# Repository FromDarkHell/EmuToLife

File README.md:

## EmuToLife

EmuToLife is a USB emulator for LEGO Dimensions, Disney Infinity, *and* [Kamen Rider Summonride](https://kamenrider.fandom.com/wiki/Kamen_Rider_Summonride).

It lets you use a Raspberry Pi Pico 2W (or W) as a replacement for an official toys-to-life pad. 
With this, you can play the game on PS3/Wii U/PS4, *or* (retail!) Xbox 360, without the original playpad.

### Setup

1. Purchase a Pi Pico 2W, and plug it in while holding the BOOTSEL button
2. Drag/drop the `.uf2` (available on Github Releases) onto the new USB device
    - If successful, the Pico will restart.
3. On the first boot, the Pico will create a new WiFi network named `captive`.
    - Connect to the `captive` WiFi network, and it will bring you to a captive portal

4. From here, it will restart, and conect to your home WiFi.
5. Then, afterwards, you can connect to it via mDNS by going to `emupad.local` in a browser.

### Features

- Wi-Fi captive portal for first-time setup
- Local web UI for managing the toy/character portal (spawning tags, etc.)
- Tag reading/writing/etc handled by my [ToysToLifeLib](https://github.com/FromDarkHell/ToysToLifeLib) library
- Full **retail** Xbox 360 support, powered by [libxsm3](https://github.com/InvoxiPlayGames/libxsm3/) by [InvoxiPlayGames](https://github.com/InvoxiPlayGames)

### License

This project is licensed using [MIT](/LICENSE.md)
- This project directly includes [libxsm3](https://github.com/InvoxiPlayGames/libxsm3/), which is licensed under GNU Lesser General Public License version 2.1
    * Additionally, libxsm3 uses [ExCrypt](https://github.com/emoose/ExCrypt), licensed under the 3-clause BSD license
- A large chunk of the LEGO Dimensions implementation is based on [Berny23/LD-ToyPad-Emulator](https://github.com/Berny23/LD-ToyPad-Emulator/), alongside [node-ld](https://github.com/Berny23/node-ld)

### Support

If you for some reason want to support me financially for this project (or others I make), you can donate to me via [ko-fi](https://ko-fi.com/fromdarkhell) or [Patreon](https://patreon.com/fromdarkhell).

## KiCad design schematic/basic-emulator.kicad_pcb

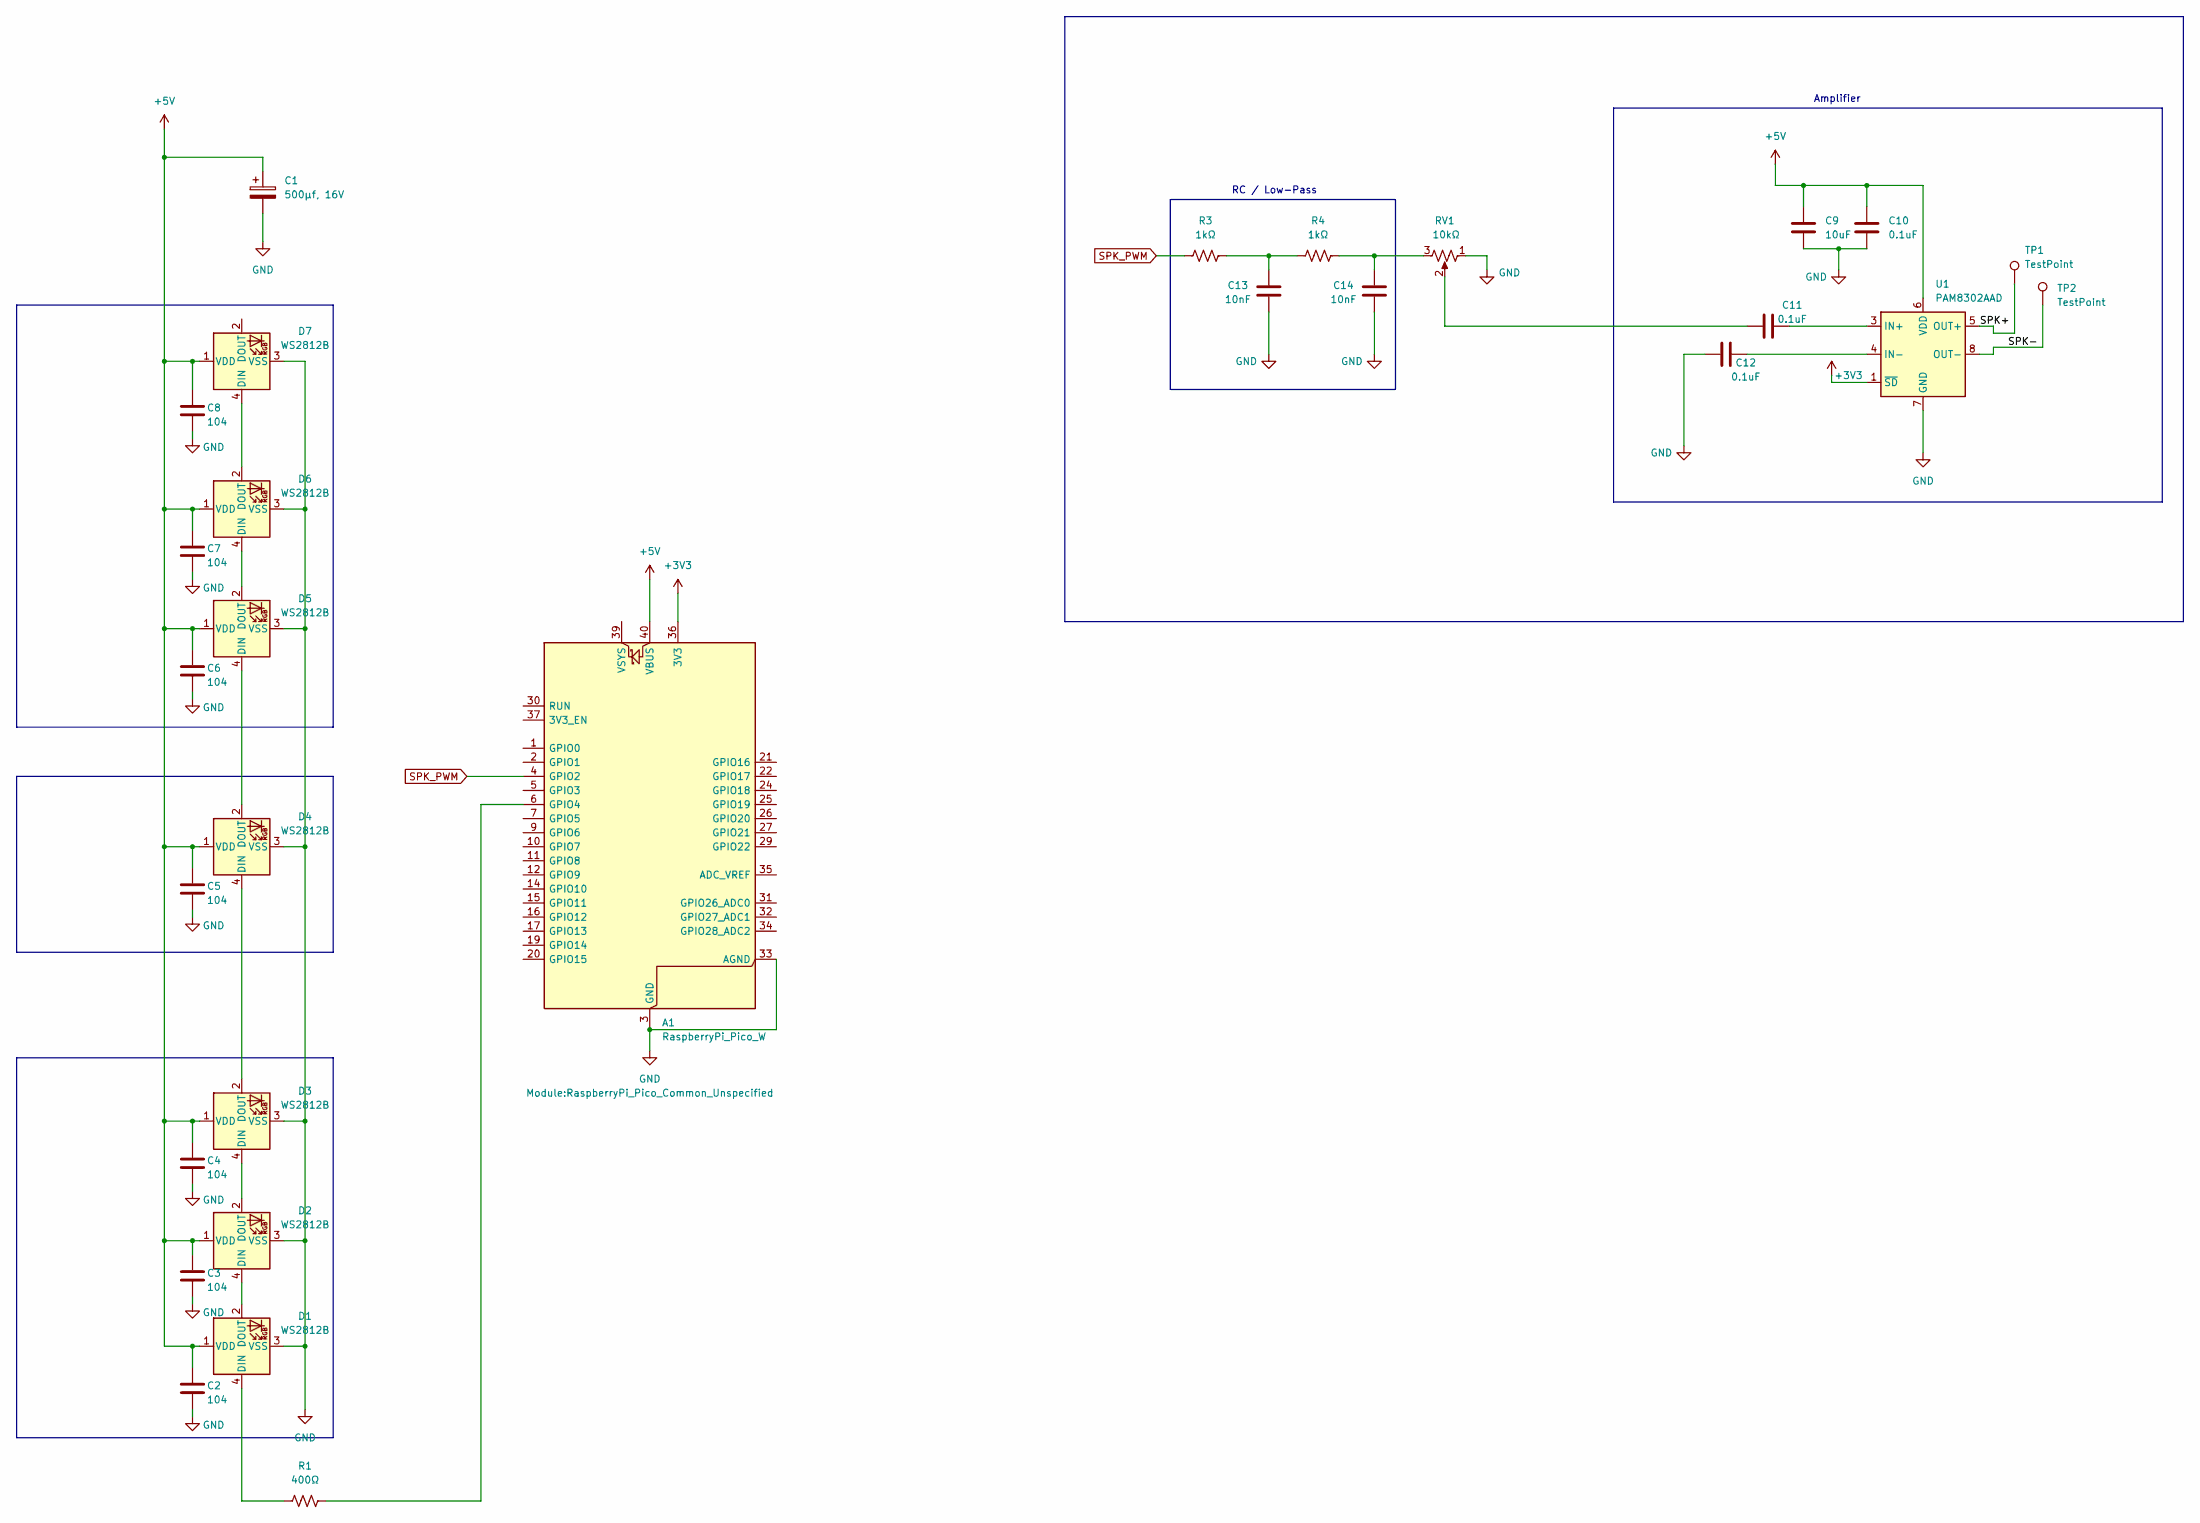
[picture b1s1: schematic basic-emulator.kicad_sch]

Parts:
A1: RaspberryPi_Pico_W; RaspberryPi_Pico_Common_Unspecified
C1: 500µf, 16V; CP_Radial_D8.0mm_P5.00mm
C2, C3, C4, C5, C6, C7, C8: 104; C_1206_3216Metric_Pad1.33x1.80mm_HandSolder
C9: 10uF; C_0603_1608Metric_Pad1.08x0.95mm_HandSolder
C10, C11, C12: 0.1uF; C_0603_1608Metric_Pad1.08x0.95mm_HandSolder
C13, C14: 10nF; C_0603_1608Metric_Pad1.08x0.95mm_HandSolder
D1, D2, D3, D4, D5, D6, D7: WS2812B; LED_WS2812B_PLCC4_5.0x5.0mm_P3.2mm
R1: 400Ω; R_1206_3216Metric_Pad1.30x1.75mm_HandSolder
R3, R4: 1kΩ; R_0603_1608Metric_Pad0.98x0.95mm_HandSolder
RV1: 10kΩ; Potentiometer_Bourns_3314G_Vertical
TP1, TP2: TestPoint; TestPoint_Pad_D2.0mm
U1: PAM8302AAD; SOIC-8_3.9x4.9mm_P1.27mm

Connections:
+3V3: A1.36 (3V3), U1.1 (~SD)
+5V: A1.40 (VBUS), C1.1, C2.1, C3.1, C4.1, C5.1, C6.1, C7.1, C8.1, C9.1, C10.1, D1.1 (VDD), D2.1 (VDD), D3.1 (VDD), D4.1 (VDD), D5.1 (VDD), D6.1 (VDD), D7.1 (VDD), U1.6 (VDD)
/SPK+: TP1.1 (1_1), U1.5 (OUT+)
/SPK-: TP2.1 (1_1), U1.8 (OUT-)
GND: A1.3 (GND), A1.8 (GND), A1.13 (GND), A1.18 (GND), A1.23 (GND), A1.28 (GND), A1.33 (AGND), A1.38 (GND), C1.2, C2.2, C3.2, C4.2, C5.2, C6.2, C7.2, C8.2, C9.2, C10.2, C12.1, C13.2, C14.2, D1.3 (VSS), D2.3 (VSS), D3.3 (VSS), D4.3 (VSS), D5.3 (VSS), D6.3 (VSS), D7.3 (VSS), RV1.1, U1.7 (GND)
unnamed: A1.6 (GPIO4), R1.2
unnamed: C11.1, RV1.2
unnamed: C13.1, R3.2, R4.1
unnamed: C14.1, R4.2, RV1.3
unnamed: D1.4 (DIN), R1.1
unnamed: D1.2 (DOUT), D2.4 (DIN)
unnamed: D2.2 (DOUT), D3.4 (DIN)
unnamed: D3.2 (DOUT), D4.4 (DIN)
unnamed: D4.2 (DOUT), D5.4 (DIN)
unnamed: D5.2 (DOUT), D6.4 (DIN)
unnamed: D6.2 (DOUT), D7.4 (DIN)
unnamed: C11.2, U1.3 (IN+)
unnamed: C12.2, U1.4 (IN-)
SPK_PWM: A1.4 (GPIO2), R3.1

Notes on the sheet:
RC / Low-Pass
Amplifier

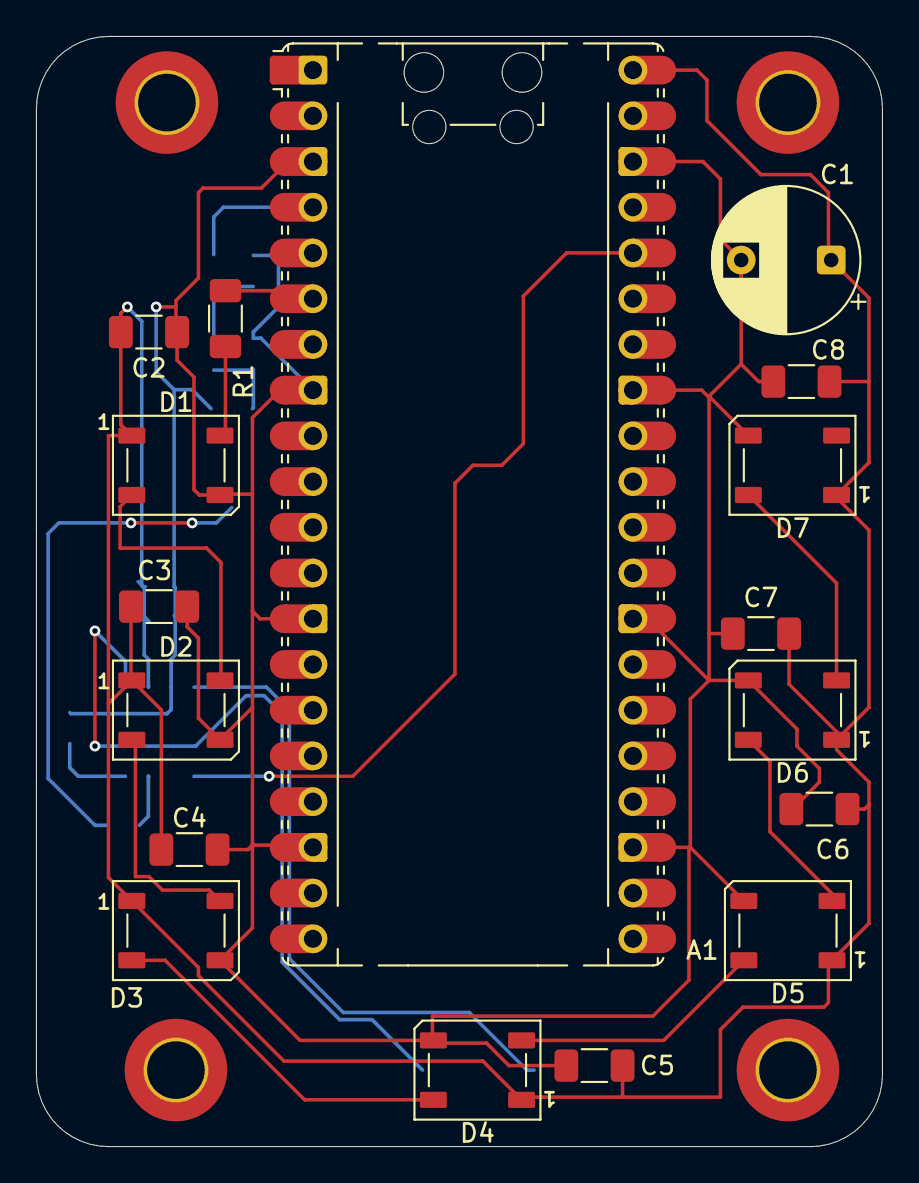
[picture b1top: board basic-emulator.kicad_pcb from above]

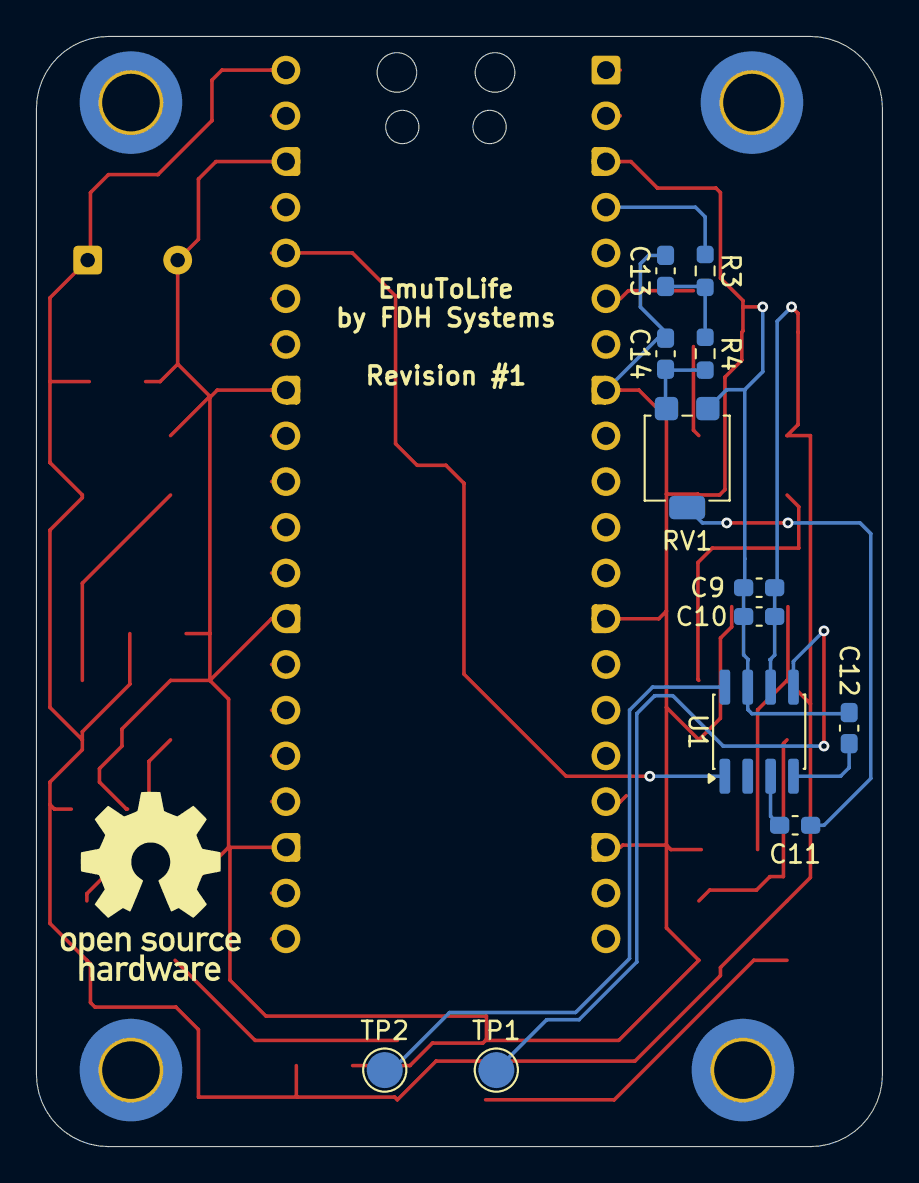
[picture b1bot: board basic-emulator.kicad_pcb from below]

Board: 2 copper layers, 47.0 x 61.7 mm, 29 parts (12 on the bottom side), 19 nets.
